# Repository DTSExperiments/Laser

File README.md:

# Laser
Layout to switch a laser ON/ OFF

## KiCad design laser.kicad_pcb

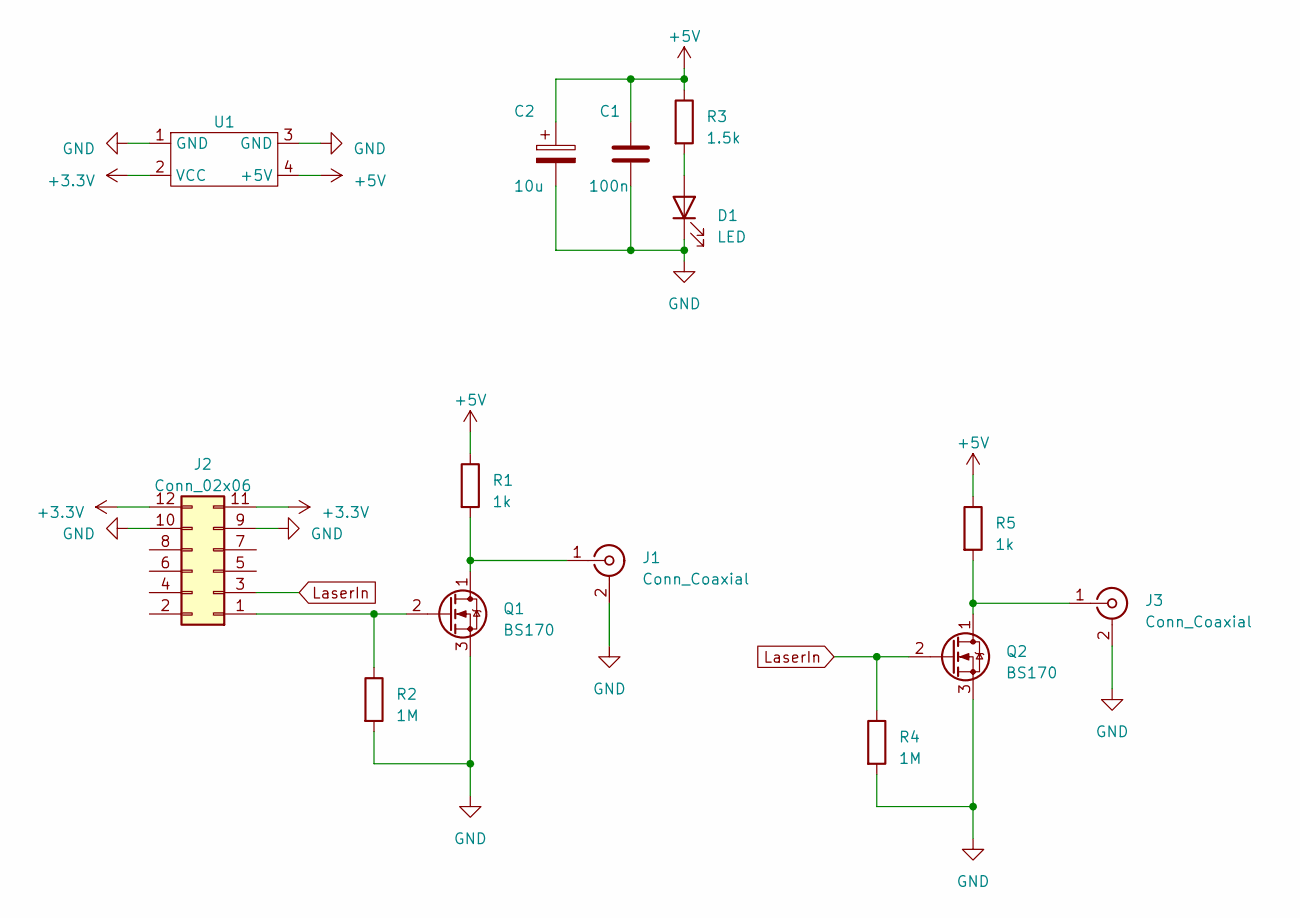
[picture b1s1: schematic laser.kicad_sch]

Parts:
C1: 100n; C_Rect_L7.0mm_W6.0mm_P5.00mm
C2: 10u; CP_Radial_D5.0mm_P2.50mm
D1: LED; LED_D3.0mm
J1, J3: Conn_Coaxial; BNC_Amphenol_B6252HB-NPP3G-50_Horizontal
J2: Conn_02x06; PinHeader_2x06_P2.54mm_Horizontal
Q1, Q2: BS170; TO-92_Inline
R1, R5: 1k; R_Axial_DIN0411_L9.9mm_D3.6mm_P20.32mm_Horizontal
R2, R4: 1M; R_Axial_DIN0411_L9.9mm_D3.6mm_P20.32mm_Horizontal
R3: 1.5k; R_Axial_DIN0411_L9.9mm_D3.6mm_P20.32mm_Horizontal
U1: tba1-0311

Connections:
+3.3V: J2.11, J2.12, U1.2 (VCC); also elsewhere on the board
+5V: C1.1, C2.1, R1.1, R3.1, R5.1, U1.4 (+5V)
GND: C1.2, C2.2, D1.1 (K), J1.2 (Ext), J2.9, J2.10, J3.2 (Ext), Q1.3 (S), Q2.3 (S), R2.2, R4.2, U1.1 (GND), U1.3 (GND); also elsewhere on the board
LaserIn: J2.3, Q2.2 (G), R4.1
unnamed: D1.2 (A), R3.2
unnamed: J1.1 (In), Q1.1 (D), R1.2
unnamed: J2.1, Q1.2 (G), R2.1
unnamed: J3.1 (In), Q2.1 (D), R5.2

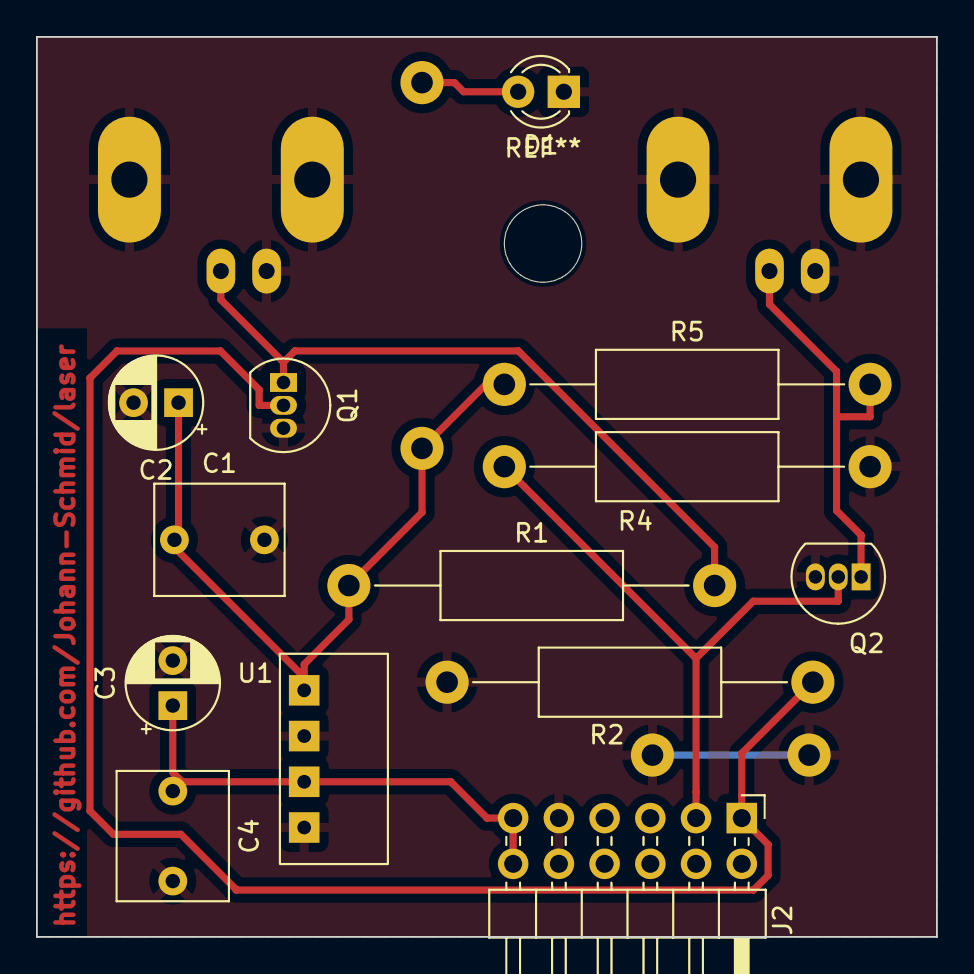
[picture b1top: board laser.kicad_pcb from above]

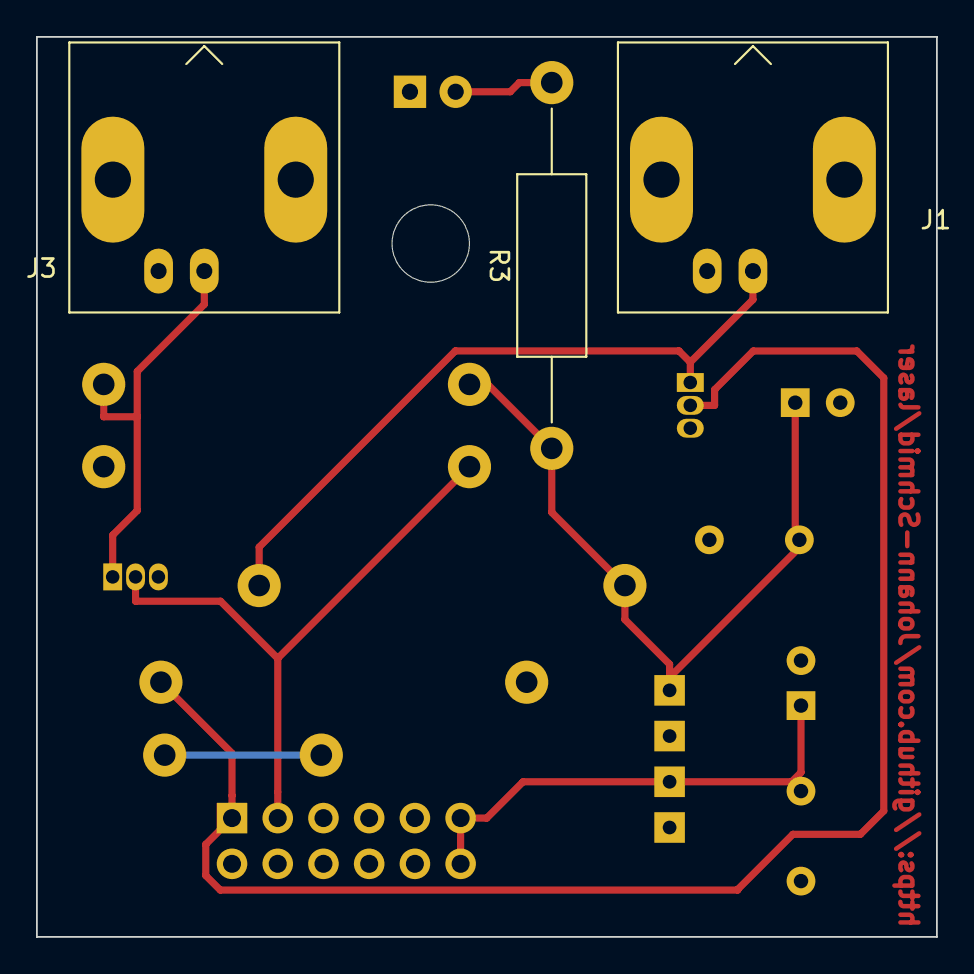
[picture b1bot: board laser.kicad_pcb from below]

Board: 2 copper layers, 50.0 x 50.0 mm, 16 parts (3 on the bottom side), 8 nets.

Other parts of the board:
C3: 10u; CP_Radial_D5.0mm_P2.50mm
C4: 100n; C_Rect_L7.0mm_W6.0mm_P5.00mm

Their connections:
+3.3V: C3.1, C4.1; also elsewhere on the board
GND: C3.2, C4.2; also elsewhere on the board

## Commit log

2023-05-25 insert C
2023-06-15 change the bnc connector of the backplane
    change the bnc connector of the backplane
2023-06-15 mounting hole
2023-06-15 insert pdfs
